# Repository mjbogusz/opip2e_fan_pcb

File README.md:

# opip2e_fan_pcb
PWM fan controller board for OrangePi Plus 2E

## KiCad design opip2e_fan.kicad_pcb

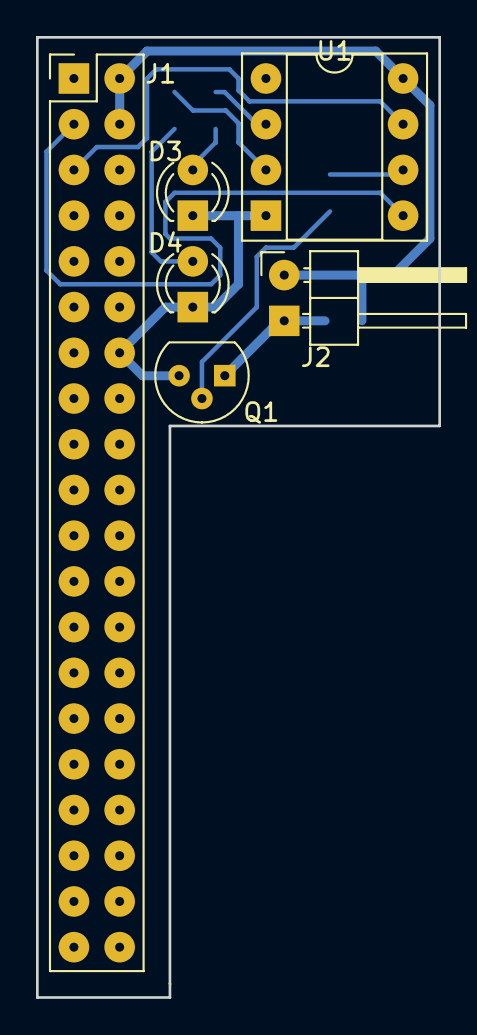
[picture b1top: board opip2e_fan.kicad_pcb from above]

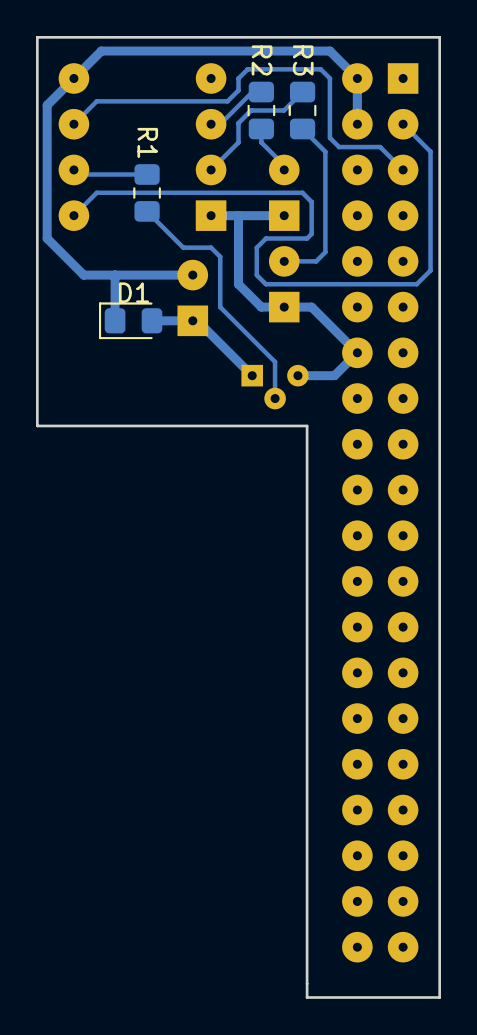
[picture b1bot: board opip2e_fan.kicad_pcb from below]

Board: 2 copper layers, 22.4 x 53.3 mm, 10 parts (4 on the bottom side), 11 nets.

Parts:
D1: D; D_0805_2012Metric_Pad1.15x1.40mm_HandSolder
D3, D4: LED; LED_D3.0mm
J1: Conn_02x20_Odd_Even; PinHeader_2x20_P2.54mm_Vertical
J2: Conn_01x02_Male; PinHeader_1x02_P2.54mm_Horizontal
Q1: Q_NPN_CBE; TO-92
R1, R2, R3: R; R_0805_2012Metric_Pad1.15x1.40mm_HandSolder
U1: ATtiny25-20PU; DIP-8_W7.62mm_Socket

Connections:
+5V: D1.1, J1.2, J1.4, J2.1, U1.8
GND: D3.1, D4.1, J1.14, Q1.3, U1.4
I2C_SCL: J1.5, U1.7
I2C_SDA: J1.3, U1.5
LED1: R2.2, U1.2
LED2: R3.2, U1.3
unnamed: D1.2, J2.2, Q1.1
unnamed: D3.2, R2.1
unnamed: D4.2, R3.1
unnamed: Q1.2, R1.1
PWM: R1.2, U1.6

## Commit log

2018-08-01 initial version
2018-08-01 improved pads/vias
